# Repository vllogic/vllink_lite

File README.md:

## 广告-超高性价比升级版USB高速无线调试器
[Vllink Basic](https://item.taobao.com/item.htm?spm=a1z10.1-c.w4004-22276990003.2.3f9b3ec9URpt5t&id=661712953813)

----------------------

# Vllink Lite

## 简介

Vllink Lite是一款低成本高性能开源调试器。**在PCBA成本控制在￥5.0以内的同时，SWD调试速度可达Jlink V8的125%**。目前调试器主控可选GD32F350G8U6/GD32F350C8T6/GD32E103Tx/GD32E103Cx，并提供对应的硬件图纸，现阶段建议使用**GD32F350**方案。

## 硬件参考设计

### 1. [Vllink Lite.R4.GD32F350xx](https://github.com/vllogic/vllink_lite/tree/master/hardware/vllink_lite.r4.gd32f350xx)
GD32F350G8淘宝零售价格已低于￥3.8，SOF校准免晶振，适合作为成本敏感的集成式调试器。

### 2. [Vllink Lite.R4.GD32E103Tx](https://github.com/vllogic/vllink_lite/tree/master/hardware/vllink_lite.r4.gd32e103tx)
相比GD32F350，拥有更大RAM与ROM，预留IO连接SPI Flash。**需要注意的是，GD32E103的USB部分尚存BUG，当DAP与CDC同时使用时，二者数据会生产干扰，目前不建议日常使用。**

### 仿真及实拍图

## 基本功能

* WEBDFU固件更新，按住按键连接Win10电脑，再使用Chrome浏览器打开更新页面即可 [WebDFU@Github](https://devanlai.github.io/webdfu/dfu-util/)或[WebDFU@Gitee](https://talpachen.gitee.io/webdfu/dfu-util/)
* CMSIS-DAP V2协议（Win10免驱）接口，提供SWD及JTAG接口，已支持IAR for ARM（版本8.32.1及以上）、MDK-ARM（版本5.29及以上）、[PyOCD](https://github.com/mbedmicro/pyOCD)、[OpenOCD](https://github.com/vllogic/openocd_cmsis-dap_v2)。具体配置方式可参看[IDE使用教程](https://github.com/vllogic/vllink_lite/blob/master/doc/ide_guide.md)
* CMSIS-DAP V2的SWO功能，在MDK-ARM下测试可用
* CDC-UART，连接硬件串口：`TXD` `RXD`

## ~~额外功能（限GD32E103，计划中）~~
* ~~内置SWD Host、JTAG Host~~
* ~~支持RAMIO，即通过调试口访问目标芯片的特定RAM，实现数据交互，类似RTT(J-Link)及Nuconsole(Nu-Link)~~
* ~~第二路复用串口，TX:`TRST`、RX:`TDO/SWO`~~
* ~~CDC-Shell，简易Shell，用以访问第二路串口或者RAMIO~~

## 调试速度测试

* 优化底层传输协议，尽量使用SPI通讯，IAR默认速率下对SRAM的读写速度可达270KB/S(SWD)或200KB/S(JTAG)，相比DAPLink（CMSIS-DAP V2），大约提升一倍。如果使用优化版的OpenOCD，读写速度可达400KB/s以上。[与主流调试器对比](https://github.com/vllogic/vllink_lite/blob/master/hardware/vllink_lite.r3/speed_test.md)

## 硬件制作

[原理图及PCBA制作资料](https://github.com/vllogic/vllink_lite/tree/master/hardware)

[固件](https://github.com/vllogic/vllink_lite/releases)

## 开发平台

* [Versaloon Software Framework](https://github.com/vsfteam/vsf)
* KiCAD
* IAR for ARM 8.40.2 + [GD32F3x0/GD32E10x AddOn](http://www.gd32mcu.com/cn/download)
* GNU Arm Embedded Toolchain + Cmake + Ninja

## 远景
* 支持简易脚本及自动化配置功能，利用WebUSB接口配合网页端工具，通过载入IAR或Keil的芯片描述文件，自动完成对应芯片的离线编程配置

## 授权
* [Versaloon Software Framework](https://github.com/vsfteam/vsf) `Apache-2.0 License`
* [CMSIS DAP](https://github.com/ARM-software/CMSIS_5) `Apache-2.0 License`
* Other ALL `GPL-3.0 License`

## 交流

欢迎加入QQ群：512256420

## 硬件获得渠道

* JLC 5元打样 + 淘宝买MCU

## 其他

* [CMSIS-DAP V2在Windows 7下使用](http://vllogic.com/software/windows7_driver.html)

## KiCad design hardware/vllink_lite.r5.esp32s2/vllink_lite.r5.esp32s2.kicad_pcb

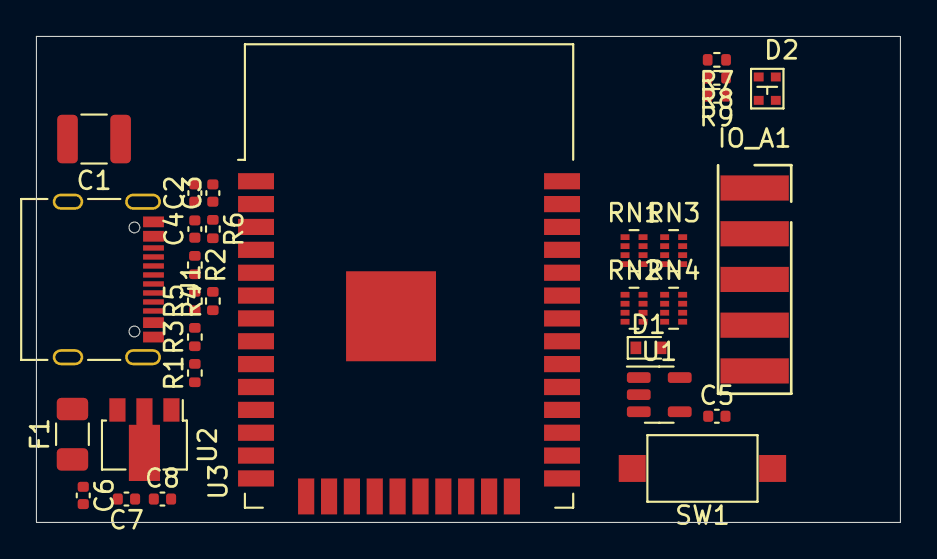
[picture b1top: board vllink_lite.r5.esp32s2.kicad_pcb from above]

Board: 2 copper layers, 48.0 x 27.0 mm, 31 parts (1 on the bottom side), 38 nets, no tracks yet.

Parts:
C1: 100uF,6.3V; C_1210_3225Metric
C2: 1uF; C_0402_1005Metric
C3, C4, C5, C8: 0.1uF; C_0402_1005Metric
C6, C7: 4.7uF; C_0402_1005Metric
D1: RB521S30; D_SOD-523
D2: LED_RABG; KO-1615RGB-2C
F1: Polyfuse,2A; Fuse_1206_3216Metric
IO_A1: Conn_01x05; PinSocket_1x5_P2.54mm_SMD
IO_B1: Conn_01x05; PinSocket_1x5_P2.54mm_SMD
J1: USB_C_Receptacle_USB2.0; USB_C_Receptacle_Palconn_UTC16-G
R1: 0; R_0402_1005Metric
R2, R3: 5.1k; R_0402_1005Metric
R4, R5: 22; R_0402_1005Metric
R6: 10k; R_0402_1005Metric
R7, R8, R9: 4.7k; R_0402_1005Metric
RN1, RN2: 220; R_Array_Concave_4x0402
RN3, RN4: 220k; R_Array_Concave_4x0402
SW1: SW_Push; SW_SPST_CK_RS282G05A3
U1: 74AHC1G08; SOT-23-5
U2: AP1117-3.3; SOT-89-3
U3: ESP32-S2-SOLO(-U); ESP32-WROOM-32

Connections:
/CHIP_EN: C4.1, R6.2, U3.3
/EXT5V: F1.2, J1.A4, J1.A9, J1.B4, J1.B9
/FSPI_CLK: RN1.1, U3.19, U3.27
/FSPI_MISO_A: RN2.1, U3.20
/FSPI_MISO_B: D1.1, RN1.3, U3.28
/FSPI_MOSI_A: RN1.4, U3.18
/FSPI_MOSI_B: U1.1, U3.26
/GPIO01: RN2.3, U3.37
/GPIO38: RN1.2, U3.29
/IOSPI_MISO: U1.2, U3.17
/KEY: SW1.2, U3.24
/LED_B: R7.2, U3.23
/LED_G: R8.2, U3.22
/LED_R: R9.2, U3.21
/RX1: IO_B1.5, RN2.7, RN4.2
/RXD0: RN2.2, U3.34
/SHIELD: J1.S1, R1.1
/SRST|SWRST: IO_A1.4, RN2.6, RN4.3
/TCK|SWCLK: IO_A1.3, RN1.8, RN3.1
/TDI: IO_A1.1, RN1.5, RN3.4
/TDO|RX2: IO_A1.5, RN2.8, RN4.1
/TMS|SWDIO: IO_A1.2, RN1.6, RN3.3
/TRST|TX2: IO_B1.3, RN1.7, RN3.2
/TX1: IO_B1.4, RN2.5, RN4.4
/TXD0: RN2.4, U3.35
/USB_5V: C6.1, F1.1, U2.3
/USB_DM: R4.1, U3.12
/USB_DP: R5.1, U3.13
GND: C1.2, C2.2, C3.2, C4.2, C5.2, C6.2, C7.2, C8.2, IO_B1.2, J1.A1, J1.A8, J1.A12, J1.B1, J1.B8, J1.B12, R1.2, R2.1, R3.1, RN3.5, RN3.6, RN3.7, RN3.8, RN4.5, RN4.6, RN4.7, RN4.8, SW1.1, U1.3, U2.1, U3.1, U3.15, U3.38, U3.39
unnamed: D1.2, U1.4
unnamed: D2.1, R9.1
unnamed: D2.3, R7.1
unnamed: D2.4, R8.1
unnamed: J1.A5, R2.2
unnamed: J1.A6, J1.B6, R5.2
unnamed: J1.A7, J1.B7, R4.2
unnamed: J1.B5, R3.2
VCC: C1.1, C2.1, C3.1, C5.1, C7.1, C8.1, D2.2, IO_B1.1, R6.1, U1.5, U2.2, U3.2

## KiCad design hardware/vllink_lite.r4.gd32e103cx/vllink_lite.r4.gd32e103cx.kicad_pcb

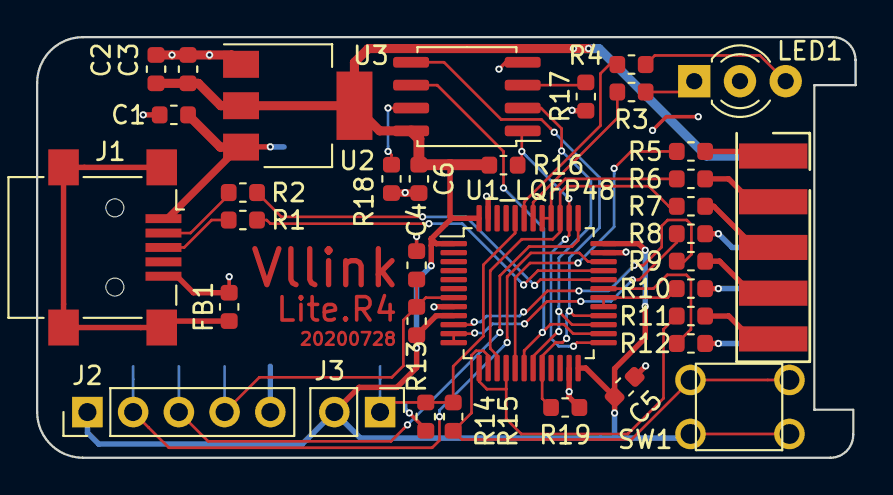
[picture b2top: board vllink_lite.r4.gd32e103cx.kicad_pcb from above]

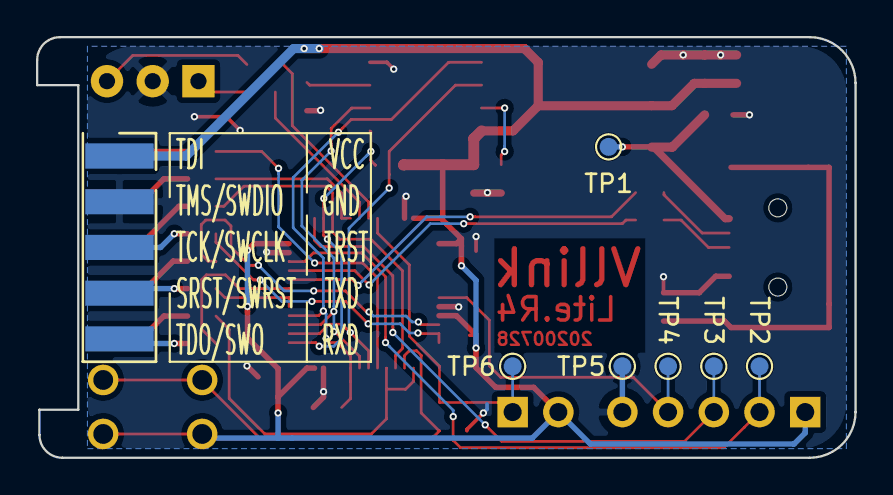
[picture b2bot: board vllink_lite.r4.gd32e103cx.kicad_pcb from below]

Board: 2 copper layers, 45.5 x 23.4 mm, 42 parts (7 on the bottom side), 39 nets.

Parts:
C1, C2: 4.7uF; C_0603_1608Metric
C3, C4, C5, C6: 0.1uF; C_0603_1608Metric
FB1: 100R@100M; L_0603_1608Metric
IO_A1: Conn_01x05; PinSocket_1x5_P2.54mm_SMD
IO_B1: Conn_01x05; PinSocket_1x5_P2.54mm_SMD
J1: USB_B_Mini; USB_Mini-B_Lumberg_2486_01_Horizontal
J2: Conn_01x05; PinHeader_1x05_P2.54mm_Vertical
J3: Conn_01x02; PinHeader_1x02_P2.54mm_Vertical
LED1: LED_Dual_ACA; LED_D3.0mm-3
R1, R2: 22; R_0603_1608Metric
R3, R4, R13, R14: 4.7k; R_0603_1608Metric
R5, R6, R7, R8, R9, R10, R11, R12: 150; R_0603_1608Metric
R15: 22, NC; R_0603_1608Metric
R16, R17, R18, R19: 10k; R_0603_1608Metric
SW1: SW_Push; SW_PUSH_4.5mm_Hxx
TP1, TP2, TP3, TP4, TP5, TP6: TestPoint; TestPoint_Pad_D1.0mm
U1_LQFP48: GD32E103Cx; LQFP-48_7x7mm_P0.5mm
U2: AP1117-33; SOT-223-3_TabPin2
U3: W25Q64; SOIC-8_P1.27mm_Common

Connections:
/BOOT0: J3.1, R14.1, R15.1, TP6.1, U1_LQFP48.44
/CK_OUT: R10.1, U1_LQFP48.29, U1_LQFP48.30
/IO_RST: R9.2, U1_LQFP48.10
/IO_TRST: R8.1, U1_LQFP48.11, U1_LQFP48.12
/KEY: R15.2, SW1.1, U1_LQFP48.14
/LED_G: R4.1, U1_LQFP48.43
/LED_R: R3.1, U1_LQFP48.42
/RST: C4.1, J2.4, R13.2, TP4.1, U1_LQFP48.7
/RXD: R12.1, U1_LQFP48.31
/SPI0_CLK: R7.2, U1_LQFP48.15, U1_LQFP48.39
/SPI00_MISO: R11.2, U1_LQFP48.13, U1_LQFP48.16
/SPI00_MOSI: R5.2, U1_LQFP48.17
/SPI1_CLK: U1_LQFP48.18, U1_LQFP48.26, U3.6
/SPI1_CS: R16.2, U1_LQFP48.25, U1_LQFP48.38, U3.1
/SPI01_MISO: R6.2, U1_LQFP48.40, U1_LQFP48.41
/SPI1_MISO: U1_LQFP48.19, U1_LQFP48.27, U3.2
/SPI1_MOSI: R19.1, U1_LQFP48.20, U1_LQFP48.28, U3.5
/SWCLK: J2.3, TP3.1, U1_LQFP48.37
/SWDIO: J2.2, TP2.1, U1_LQFP48.34
/USBD_DM: R2.1, U1_LQFP48.32
/USBD_DP: R1.1, U1_LQFP48.33
/USB_5V: C1.1, J1.1, TP1.1, U2.3
/VCC: C2.1, C3.1, C5.1, C6.1, IO_B1.1, J2.1, J3.2, R13.1, R16.1, SW1.2, U1_LQFP48.1, U1_LQFP48.9, U1_LQFP48.24, U1_LQFP48.36, U1_LQFP48.48, U2.2, U3.8
GND: C1.2, C2.2, C3.2, C4.2, C5.2, C6.2, FB1.2, IO_B1.2, J1.5, J2.5, LED1.2, R14.2, R17.1, R18.1, R19.2, TP5.1, U1_LQFP48.8, U1_LQFP48.23, U1_LQFP48.35, U1_LQFP48.47, U2.1, U3.4
unnamed: FB1.1, J1.6
unnamed: IO_A1.1, R5.1
unnamed: IO_A1.2, R6.1
unnamed: IO_A1.3, R7.1
unnamed: IO_A1.4, R9.1
unnamed: IO_A1.5, R11.1
unnamed: IO_B1.3, R8.2
unnamed: IO_B1.4, R10.2
unnamed: IO_B1.5, R12.2
unnamed: J1.2, R2.2
unnamed: J1.3, R1.2
unnamed: LED1.1, R3.2
unnamed: LED1.3, R4.2
unnamed: R17.2, U3.3
unnamed: R18.2, U3.7

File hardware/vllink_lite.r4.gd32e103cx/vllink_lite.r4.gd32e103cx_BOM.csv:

"Comment","Description","Designator","Footprint","LibRef","Pins","Quantity","PartNumber","url",
"4.7uF","desc","C2,C1,","C_0603_1608Metric","libref","2","2","","",
"0.1uF","desc","C6,C5,C4,C3,","C_0603_1608Metric","libref","2","4","","",
"100R@100M","desc","FB1,","L_0603_1608Metric","libref","2","1","","",
"Conn_01x05","desc","IO_A1,","PinSocket_1x5_P2.54mm_SMD","libref","5","1","","",
"150","desc","R12,R11,R10,R9,R8,R7,R6,R5,","R_0603_1608Metric","libref","2","8","","",
"4.7k","desc","R14,R13,R4,R3,","R_0603_1608Metric","libref","2","4","","",
"22, NC","desc","R15,","R_0603_1608Metric","libref","2","1","","",
"10k","desc","R19,R18,R17,R16,","R_0603_1608Metric","libref","2","4","","",
"22","desc","R2,R1,","R_0603_1608Metric","libref","2","2","","",
"GD32E103Cx","desc","U1_LQFP48,","LQFP-48_7x7mm_P0.5mm","libref","48","1","","",
"AP1117-33","desc","U2,","SOT-223-3_TabPin2","libref","4","1","","",
"W25Q64","desc","U3,","SOIC-8_P1.27mm_Common","libref","8","1","","",
"Conn_01x05","desc","IO_B1,","PinSocket_1x5_P2.54mm_SMD","libref","5","1","","",
"TestPoint","desc","TP6,TP5,TP4,TP3,TP2,TP1,","TestPoint_Pad_D1.0mm","libref","1","6","","",
"Through Hole Items ",
"USB_B_Mini","desc","J1,","USB_Mini-B_Lumberg_2486_01_Horizontal","libref","11","1","","",
"Conn_01x05","desc","J2,","PinHeader_1x05_P2.54mm_Vertical","libref","5","1","","",
"Conn_01x02","desc","J3,","PinHeader_1x02_P2.54mm_Vertical","libref","2","1","","",
"LED_Dual_ACA","desc","LED1,","LED_D3.0mm-3","libref","3","1","","",
"SW_Push","desc","SW1,","SW_PUSH_4.5mm_Hxx","libref","4","1","","",

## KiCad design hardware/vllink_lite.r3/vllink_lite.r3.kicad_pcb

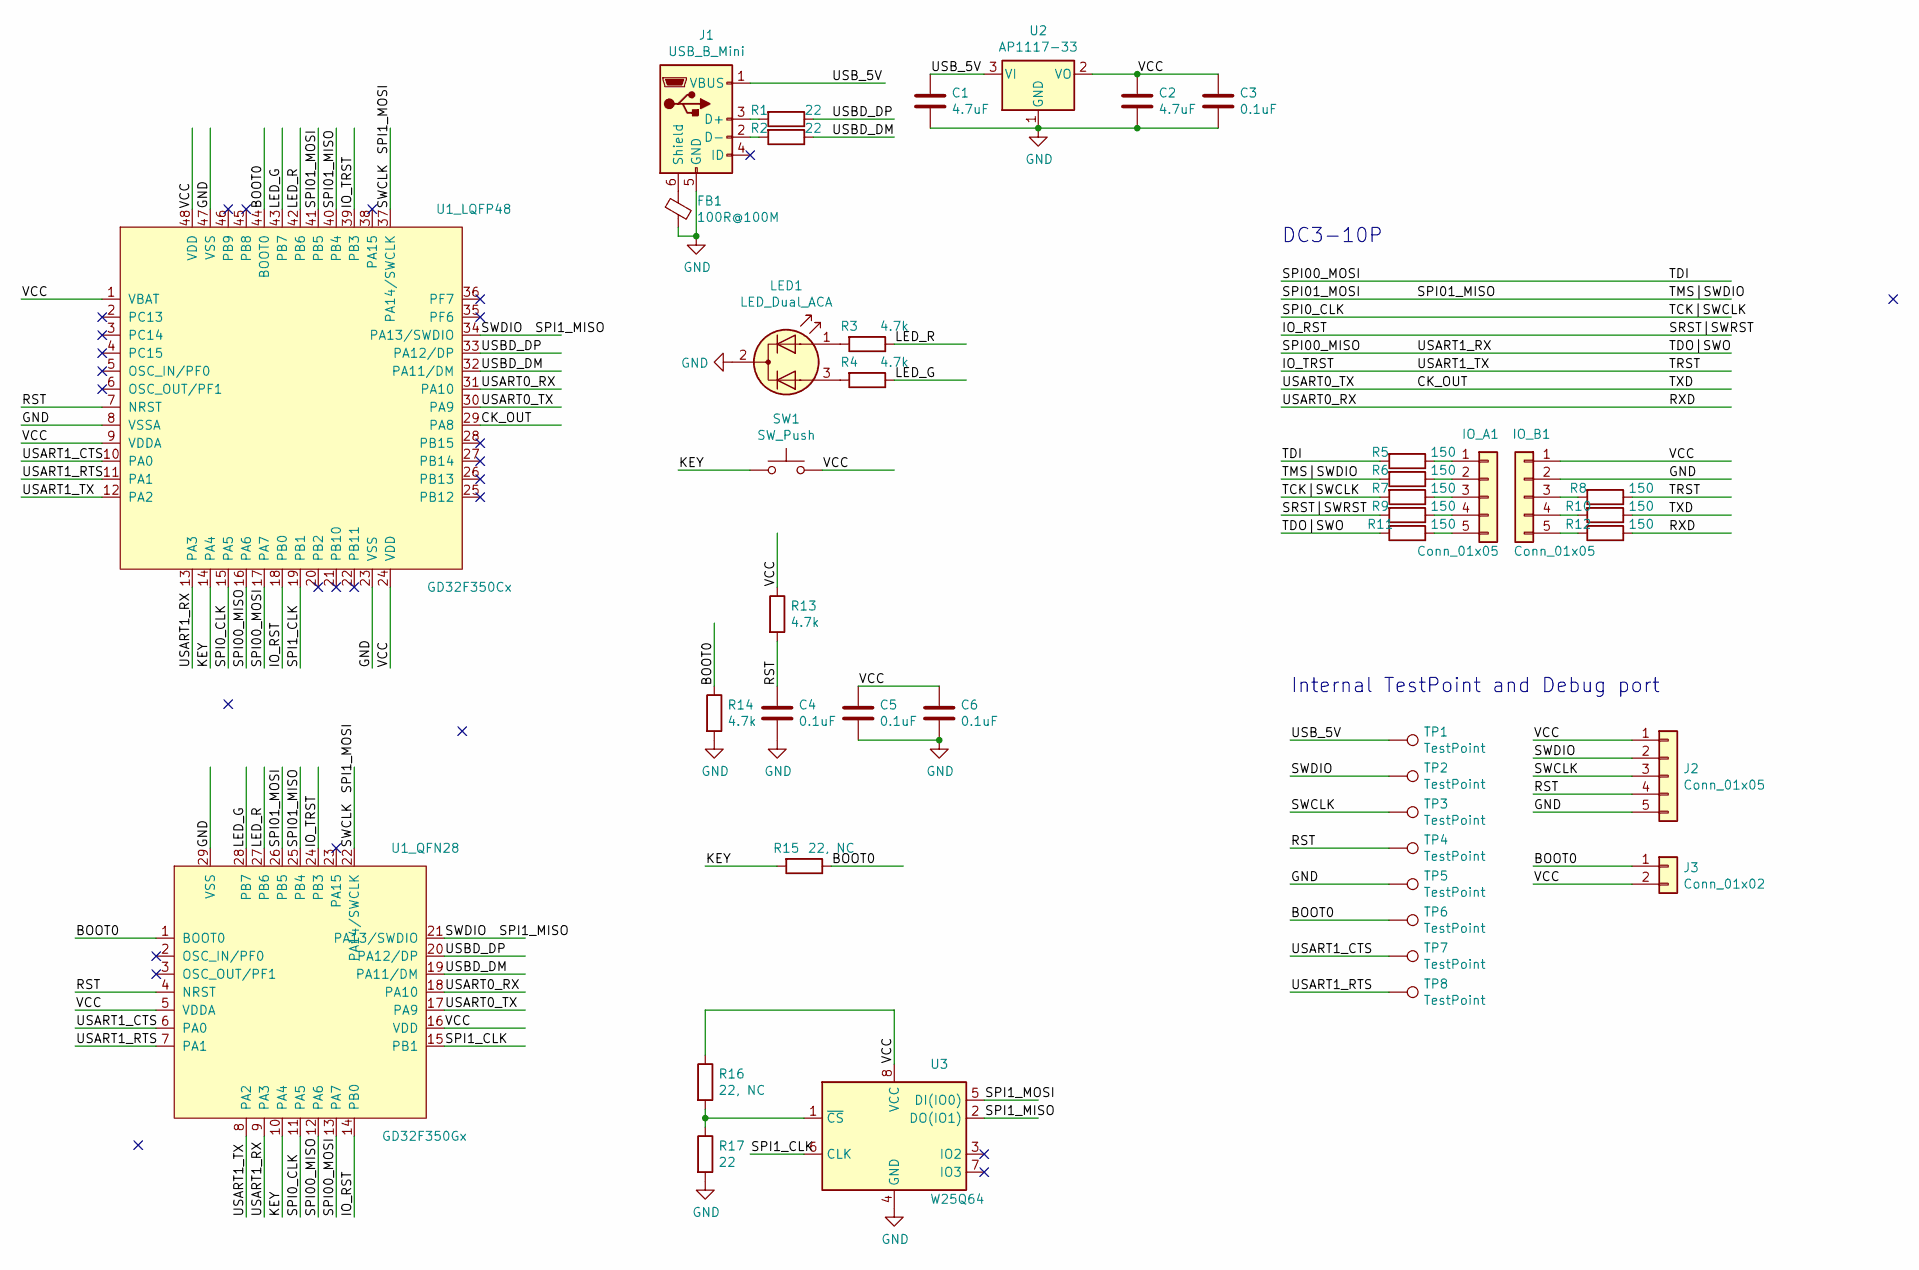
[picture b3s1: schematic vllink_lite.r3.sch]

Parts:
C1, C2: 4.7uF; C_0603_1608Metric
C3, C4, C5, C6: 0.1uF; C_0603_1608Metric
FB1: 100R@100M; L_0603_1608Metric
IO_A1: Conn_01x05; PinSocket_1x5_P2.54mm_SMD
IO_B1: Conn_01x05; PinSocket_1x5_P2.54mm_SMD
J1: USB_B_Mini; USB_Mini-B_Lumberg_2486_01_Horizontal
J2: Conn_01x05; PinHeader_1x05_P2.54mm_Vertical
J3: Conn_01x02; PinHeader_1x02_P2.54mm_Vertical
LED1: LED_Dual_ACA; LED_D3.0mm-3
R1, R2, R17: 22; R_0603_1608Metric
R3, R4, R13, R14: 4.7k; R_0603_1608Metric
R5, R6, R7, R8, R9, R10, R11, R12: 150; R_0603_1608Metric
R15, R16: 22, NC; R_0603_1608Metric
SW1: SW_Push; SW_PUSH_4.5mm_Hxx
TP1, TP2, TP3, TP4, TP5, TP6, TP7, TP8: TestPoint; TestPoint_Pad_D1.0mm
U1_LQFP48: GD32F350Cx; LQFP-48_7x7mm_P0.5mm
U1_QFN28: GD32F350Gx; QFN-28-1EP_4x4mm_P0.4mm_EP2.7x2.7mm
U2: AP1117-33; SOT-223-3_TabPin2
U3: W25Q64; SOIC-8_5.23x5.23mm_P1.27mm

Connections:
/BOOT0: J3.1, R14.1, R15.1, TP6.1, U1_LQFP48.44 (BOOT0), U1_QFN28.1 (BOOT0); also elsewhere on the board
/CK_OUT: R10.1, U1_LQFP48.29 (PA8), U1_LQFP48.30 (PA9), U1_QFN28.17 (PA9); also elsewhere on the board
/IO_RST: R9.2, U1_LQFP48.18 (PB0), U1_QFN28.14 (PB0); also elsewhere on the board
/IO_TRST: R8.1, U1_LQFP48.12 (PA2), U1_LQFP48.39 (PB3), U1_QFN28.8 (PA2), U1_QFN28.24 (PB3); also elsewhere on the board
/KEY: R15.2, SW1.1, U1_LQFP48.14 (PA4), U1_QFN28.10 (PA4); also elsewhere on the board
/LED_G: R4.1, U1_LQFP48.43 (PB7), U1_QFN28.28 (PB7); also elsewhere on the board
/LED_R: R3.1, U1_LQFP48.42 (PB6), U1_QFN28.27 (PB6); also elsewhere on the board
/RST: C4.1, J2.4, R13.2, TP4.1, U1_LQFP48.7 (NRST), U1_QFN28.4 (NRST); also elsewhere on the board
/RXD: R12.1, U1_LQFP48.31 (PA10), U1_QFN28.18 (PA10); also elsewhere on the board
/SPI0_CLK: R7.2, U1_LQFP48.15 (PA5), U1_QFN28.11 (PA5); also elsewhere on the board
/SPI00_MISO: R11.2, U1_LQFP48.13 (PA3), U1_LQFP48.16 (PA6), U1_QFN28.9 (PA3), U1_QFN28.12 (PA6); also elsewhere on the board
/SPI00_MOSI: R5.2, U1_LQFP48.17 (PA7), U1_QFN28.13 (PA7); also elsewhere on the board
/SPI1_CLK: U1_LQFP48.19 (PB1), U1_QFN28.15 (PB1), U3.6 (CLK); also elsewhere on the board
/SPI1_MISO: J2.2, TP2.1, U1_LQFP48.34 (PA13/SWDIO), U1_QFN28.21 (PA13/SWDIO), U3.2 (DO(IO1)); also elsewhere on the board
/SPI01_MISO: R6.2, U1_LQFP48.40 (PB4), U1_LQFP48.41 (PB5), U1_QFN28.25 (PB4), U1_QFN28.26 (PB5); also elsewhere on the board
/SPI1_MOSI: J2.3, TP3.1, U1_LQFP48.37 (PA14/SWCLK), U1_QFN28.22 (PA14/SWCLK), U3.5 (DI(IO0)); also elsewhere on the board
/USART1_CTS: TP7.1, U1_LQFP48.10 (PA0), U1_QFN28.6 (PA0); also elsewhere on the board
/USART1_RTS: TP8.1, U1_LQFP48.11 (PA1), U1_QFN28.7 (PA1); also elsewhere on the board
/USBD_DM: R2.1, U1_LQFP48.32 (PA11/DM), U1_QFN28.19 (PA11/DM); also elsewhere on the board
/USBD_DP: R1.1, U1_LQFP48.33 (PA12/DP), U1_QFN28.20 (PA12/DP); also elsewhere on the board
/USB_5V: C1.1, J1.1 (VBUS), TP1.1, U2.3 (VI)
/VCC: C2.1, C3.1, C5.1, C6.1, IO_B1.1, J2.1, J3.2, R13.1, R16.1, SW1.2, U1_LQFP48.1 (VBAT), U1_LQFP48.9 (VDDA), U1_LQFP48.24 (VDD), U1_LQFP48.48 (VDD), U1_QFN28.5 (VDDA), U1_QFN28.16 (VDD), U2.2 (VO), U3.8 (VCC); also elsewhere on the board
GND: C1.2, C2.2, C3.2, C4.2, C5.2, C6.2, FB1.2, IO_B1.2, J1.5 (GND), J2.5, LED1.2 (K), R14.2, R17.2, TP5.1, U1_LQFP48.8 (VSSA), U1_LQFP48.23 (VSS), U1_LQFP48.47 (VSS), U1_QFN28.29 (VSS), U2.1 (GND), U3.4 (GND); also elsewhere on the board
unnamed: FB1.1, J1.6 (Shield)
unnamed: IO_A1.1, R5.1
unnamed: IO_A1.2, R6.1
unnamed: IO_A1.3, R7.1
unnamed: IO_A1.4, R9.1
unnamed: IO_A1.5, R11.1
unnamed: IO_B1.3, R8.2
unnamed: IO_B1.4, R10.2
unnamed: IO_B1.5, R12.2
unnamed: J1.2 (D-), R2.2
unnamed: J1.3 (D+), R1.2
unnamed: LED1.1 (A1), R3.2
unnamed: LED1.3 (A2), R4.2
unnamed: R16.2, R17.1, U3.1 (~CS)

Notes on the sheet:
DC3-10P
Internal TestPoint and Debug port

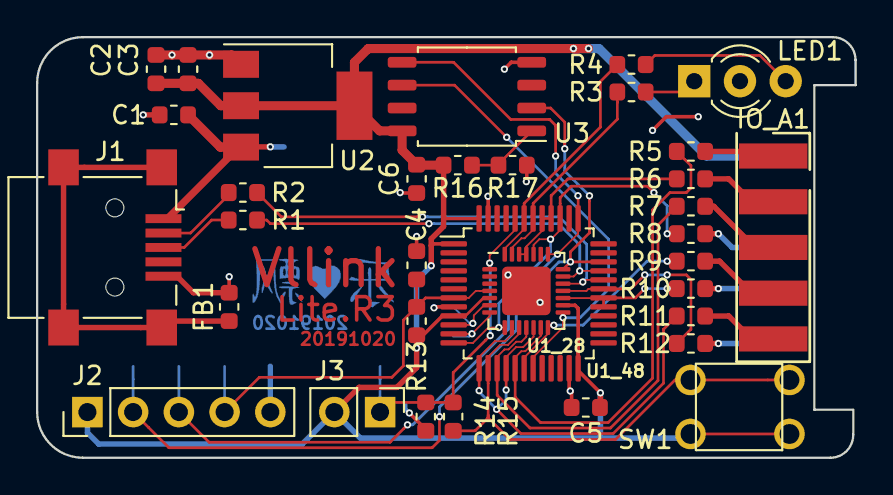
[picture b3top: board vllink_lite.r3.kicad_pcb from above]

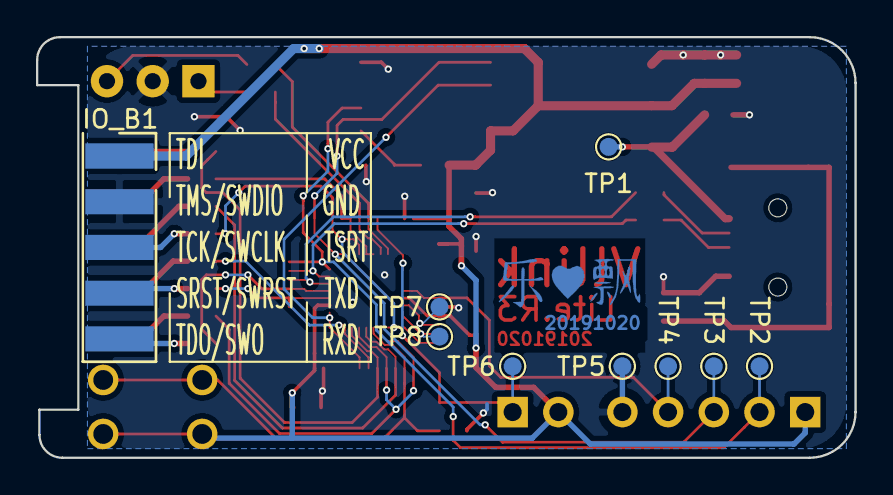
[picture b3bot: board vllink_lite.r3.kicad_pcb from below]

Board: 2 copper layers, 45.5 x 23.4 mm, 43 parts (9 on the bottom side), 37 nets.

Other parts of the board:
U1_28: GD32F350Gx; QFN-28-1EP_4x4mm_P0.4mm_EP2.7x2.7mm
U1_48: GD32F350Cx; LQFP-48_7x7mm_P0.5mm

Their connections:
/BOOT0: U1_28.1, U1_48.44; also elsewhere on the board
/CK_OUT: U1_28.17, U1_48.29, U1_48.30; also elsewhere on the board
/IO_RST: U1_28.14, U1_48.18; also elsewhere on the board
/IO_TRST: U1_28.8, U1_28.24, U1_48.12, U1_48.39; also elsewhere on the board
/KEY: U1_28.10, U1_48.14; also elsewhere on the board
/LED_G: U1_28.28, U1_48.43; also elsewhere on the board
/LED_R: U1_28.27, U1_48.42; also elsewhere on the board
/RST: U1_28.4, U1_48.7; also elsewhere on the board
/RXD: U1_28.18, U1_48.31; also elsewhere on the board
/SPI0_CLK: U1_28.11, U1_48.15; also elsewhere on the board
/SPI00_MISO: U1_28.9, U1_28.12, U1_48.13, U1_48.16; also elsewhere on the board
/SPI00_MOSI: U1_28.13, U1_48.17; also elsewhere on the board
/SPI1_CLK: U1_28.15, U1_48.19; also elsewhere on the board
/SPI1_MISO: U1_28.21, U1_48.34; also elsewhere on the board
/SPI01_MISO: U1_28.25, U1_28.26, U1_48.40, U1_48.41; also elsewhere on the board
/SPI1_MOSI: U1_28.22, U1_48.37; also elsewhere on the board
/USART1_CTS: U1_28.6, U1_48.10; also elsewhere on the board
/USART1_RTS: U1_28.7, U1_48.11; also elsewhere on the board
/USBD_DM: U1_28.19, U1_48.32; also elsewhere on the board
/USBD_DP: U1_28.20, U1_48.33; also elsewhere on the board
/VCC: U1_28.5, U1_28.16, U1_48.1, U1_48.9, U1_48.24, U1_48.48; also elsewhere on the board
GND: U1_28.29, U1_48.8, U1_48.23, U1_48.47; also elsewhere on the board

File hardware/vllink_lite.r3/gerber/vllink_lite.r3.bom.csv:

Reference, Quantity, Value, Footprint, Datasheet
C1 C2 ,2,"4.7uF","Capacitor_SMD:C_0603_1608Metric","~"
C3 C4 C5 C6 ,4,"0.1uF","Capacitor_SMD:C_0603_1608Metric","~"
FB1 ,1,"100R@100M","Inductor_SMD:L_0603_1608Metric","~"
IO_A1 IO_B1 ,2,"Conn_01x05","vllogic:PinSocket_1x5_P2.54mm_SMD","~"
J1 ,1,"USB_B_Mini","Connector_USB:USB_Mini-B_Lumberg_2486_01_Horizontal","~"
J2 ,1,"Conn_01x05","Connector_PinHeader_2.54mm:PinHeader_1x05_P2.54mm_Vertical","~"
J3 ,1,"Conn_01x02","Connector_PinHeader_2.54mm:PinHeader_1x02_P2.54mm_Vertical","~"
LED1 ,1,"LED_Dual_ACA","LED_THT:LED_D3.0mm-3","~"
R13 R14 R3 R4 ,4,"4.7k","Resistor_SMD:R_0603_1608Metric","~"
R16 R15 ,2,"22, NC","Resistor_SMD:R_0603_1608Metric","~"
R17 R1 R2 ,3,"22","Resistor_SMD:R_0603_1608Metric","~"
R5 R6 R7 R9 R11 R8 R10 R12 ,8,"150","Resistor_SMD:R_0603_1608Metric","~"
SW1 ,1,"SW_Push","vllogic:SW_PUSH_4.5mm_Hxx","~"
TP1 TP2 TP3 TP4 TP5 TP6 TP7 TP8 ,8,"TestPoint","TestPoint:TestPoint_Pad_D1.0mm","~"
U1_LQFP48 ,1,"GD32F350Cx","Package_QFP:LQFP-48_7x7mm_P0.5mm",""
U1_QFN28 ,1,"GD32F350Gx","vllogic:QFN-28-1EP_4x4mm_P0.4mm_EP2.7x2.7mm",""
U2 ,1,"AP1117-33","Package_TO_SOT_SMD:SOT-223-3_TabPin2","http://www.diodes.com/datasheets/AP1117.pdf"
U3 ,1,"W25Q64","Package_SO:SOIC-8_5.23x5.23mm_P1.27mm","http://www.winbond.com/resource-files/w25q32jv%20revg%200327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"

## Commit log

2018-11-02 Vllink Lite R2 PCB & Firmware
2018-11-02 markdown fix
2018-11-03 readme fix
2019-11-14 import sources and update vsf, wait test.
2019-11-17 CMSIS-DAP test OK
2019-11-17 add CMSIS-DAP V2 interface
2019-11-18 cmsis_dap_v2 class
2019-11-18 BOS descriptor error
2019-11-18 CMSIS-DAP v2 enumeration success
2019-11-18 remove usb request record
2019-11-18 copy daplink string
2019-11-18 CMSIS-DAP V2 IAR 8.32.3 test pass
2019-11-18 configure code optimization level
2019-11-19 remove PROJC_CFG_CMSIS_DAP_V1_SUPPORT
2019-11-19 support MDK-ARM V5.29 Educational version
2019-11-19 change link file
2019-11-19 add LICENSE
2019-11-20 remove old firmware
2019-11-22 vllink_lite.r3 sch
2019-11-22 layout vllink lite r3
2019-11-22 vllink_lite.r3 pcb finish
2019-11-23 rename
2019-11-24 Add Bootloader Project, wait test
2019-11-24 ID_DAP_Vendor30 and ID_DAP_Vendor30 cmd test pass
2019-11-24 exchange CMSIS-DAP V2 interface number with WEBUSB
2019-11-24 import firmware; remove vllink lite r2 pcb file;
2019-11-26 add GPLv3 Copyright header
2019-11-27 increase DAP_PACKET_COUNT
2019-11-28 Set theme jekyll-theme-cayman
2019-11-28 add DFU bootloader and support webusb
2019-11-28 update speed test
2019-11-30 fix gpio pulldown
2019-12-01 add pcba picture
2019-12-10 generate bom
2019-12-11 usart rxd io pullup
2019-12-11 off swd_read_quick and swd_write_quick; enable io highspeed out
2019-12-11 fix usart bug
2019-12-11 update bom
2019-12-11 revert swd_read_quick & swd_write_quick
2019-12-12 remove vllink_lite.r3.bom.csv
2019-12-25 try to support SWO; add TIMESTAMP_CLOCK
2019-12-25 review base on https://github.com/ARMmbed/DAPLink/tree/185c230c0cae00d892a1bbfe5acaa82c5493db5b/source/daplink/cmsis-dap
2020-01-02 support PROJ_CFG_EXT_IO_AUTO_CHECK
2020-01-03 add ide_guide.md
2020-01-07 swo fix
2020-01-07 support usart on/off
2020-01-16 add debug_esp32.md
2020-01-16 ide debug
2020-01-19 use no dma usart rx, miss data still
2020-01-19 add line_coding change check
2020-01-19 revert
2020-01-19 support esp32 firmware download through pySerial
2020-01-19 config usart rx dma mode: DMA_CHXCTL_CMEN | DMA_CHXCTL_HTFIE | DMA_CHXCTL_FTFIE
2020-01-19 unstable, buckup
2020-02-10 remove old vsf source
2020-02-10 import new vsf code (cmake build) from https://github.com/talpachen/vsf/tree/9e08cde47edc5f5f3cece5c4a0747ac0caff16af
2020-02-11 some gd32f350 sources
2020-02-11 auto generate compile_definitions.h
2020-02-11 move gd32f3x0 drivers in vsf
2020-02-12 fix vk_dwcotg_hw_info_t to vsf_dwcotg_hw_info_t
2020-02-12 merger gd32f330 and gd32f350 driver
2020-02-12 fix link
2020-02-13 fix __VECTOR_TABLE
2020-02-13 project file
2020-02-24 sync vsf: https://github.com/vsfteam/vsf/commit/edaf57edc705116783036a531ce042367513581a
2020-02-24 remove vsf_private
2020-02-24 update cmake
2020-02-24 iar project
2020-02-25 gd32f350 driver
2020-02-25 sync
2020-02-28 bootloader project
2020-04-06 Sync
    Revision: edaf57edc705116783036a531ce042367513581a
    Author: SimonQian <SimonQian@SimonQian.com>
    Date: 2020/2/24 0:40:09
    Message:
    update disp_sdl2, start flush thread after SDL window created
    ----
2020-05-31 add lost sources
2020-05-31 build bootloader
2020-05-31 usb init fail
2020-07-28 new board vllink_lite.r4.gd32f350xx
2020-07-28 vllink_lite.r4.gd32e103tx & vllink_lite.r4.gd32e103cx
2020-07-28 README.md
2020-07-28 sync vsf
2020-07-28 sync with https://github.com/talpachen/vsf/tree/95235c0268ee8ceaab721a87b38c7e33b37d5075
2020-07-28 add vllink_lite project
2020-07-28 dfu code
2020-07-28 cmake build
2020-07-28 cmake + arm-none-eabi-xxx build , need add uchar.h in "GNU Arm Embedded Toolchain\9 2020-q2-update\arm-none-eabi\include" ``` #ifndef _UCHAR_H #define _UCHAR_H 1
    typedef __uint_least16_t char16_t;
    typedef __uint_least32_t char32_t;
    #endif /* uchar.h */
    ```
2020-07-29 fix build error
2020-07-29 fix gd32f3x0_usb_init
2020-07-29 enable GCCFG_SOFOEN
2020-07-30 usb test pass
2020-07-30 usb transfer error
2020-07-30 GD32E103 build
2020-07-30 GCC code size optimization: https://interrupt.memfault.com/blog/code-size-optimization-gcc-flags
2020-07-30 Need Define: #define VSF_DWCOTG_DCD_CFG_AUTO_BUFFER_INIT ENABLED
2020-07-31 GD32E103 USB DFU
2020-07-31 remove #include <uchar.h>
2020-07-31 fix vk_dwcotg_usbd_ep_out_transfer
2020-07-31 support repeat download and upload
2020-08-01 backup
2020-08-06 add vllink_lite.r4.gd32e103cx.kicad_pcb
2020-08-06 vllink_lite.r4.gd32e103tx.kicad_pcb
2020-08-06 vllink_lite.r4.gd32f350xx / vllink_lite.r4.gd32e103tx / vllink_lite.r4.gd32e103cx gerbers
2020-08-31 add vllink_lite.r4.gd32e103tx.pcba.png
2020-09-13 import new vllink lite source
2020-09-15 revert sync mode
2020-09-17 fix some bug
2020-09-20 support timestamp and swo; only test on gd32e103tb;
2020-09-21 fix PCB text
2020-09-23 build vllink lite.r4 gd32e103xx firmware
2020-09-23 support cmake & gcc build
2020-09-26 basic function done
2020-09-26 add firmware
2020-10-16 optimize CDC-UART compatibility
2020-10-16 vsf_dwcotg_dcd.c fix
2020-10-16 fix firmware
2020-10-17 zlp fix
2020-10-17 update firmware
2020-10-19 fix the critical problem; fix bootloader sp check error
2020-10-19 add ams1117-adj sch for gd32e103 board
2020-10-20 revert sources
2020-10-22 revert lost doc
2020-10-23 support USB_CDCACM_REQ_SET_CONTROL_LINE_STATE; use osc ping as dtr/rts
2020-10-26 add AN00124_-USB-CDC-Class-as-Virtual-Serial-Port_2.0.2rc1.pdf
2020-11-24 vllink_lite.r5.esp32c3 prepare
2020-12-20 optimize usart rx operation
2021-01-10 sync with https://github.com/vsfteam/vsf/tree/1ce3670500fe790f923f953ae0194ba34c0e00c0
2021-01-10 sync vsf_private
2021-01-10 VSF_ARCH_RTOS_CFG_MALLOC_ALIGNED_API
2021-01-10 update projects
2021-01-10 vllink_lite.r5.esp32s2
2021-02-03 vllink_inline.r0
2021-08-15 clear interrupt flag first, because operation afterwards will maybe trigger next interrupt
2022-01-10 修复一种因未考虑到宏展开而可能引发异常的BUG
2022-01-23 add mt006 driver
2022-01-23 mt006 sch & chip TRM & ide patch
2022-01-23 create mt006 project
2022-01-23 build pass
2022-01-23 wait hardware
2022-02-01 wait test
2022-02-02 waveform ok
2022-02-02 write error
2022-02-02 not stable
2022-02-03 #define DAP_PACKET_COUNT 4
2022-02-13 ARM JTAG 调试原理
2022-02-25 increase stack
2022-02-25 fix uart
2022-02-25 mt006 support usart config reset_baud_only
2022-02-25 优化MT006串口驱动
2022-02-25 fix APP_CFG_CDCEXT_PKT_SIZE
2022-02-25 enum success
2022-02-25 enum success really
2022-02-25 定时器需要复用
2022-02-25 MT006 xmodem 1k test pass
2022-02-27 void vsf_arch_sleep(uint32_t mode) { UNUSED_PARAM(mode); //__WFE(); }
2022-02-27 off TICKCNT_ENABLE
2022-02-27 add reset
2022-03-03 usb fix
2022-04-12 build fix
2022-05-15 add "dap_srst_clear_attach_handler", support Keil "Reset and Run" after F8 downloand
2022-08-17 support windows 7
2023-03-25 remove mt006
